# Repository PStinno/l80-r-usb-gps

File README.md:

# l80-r-usb-gps
USB GPS board using the Quectel L80-R GPS module

This board makes use of the Quectel L80-R GPS module with integratred ceramic patch antenna and the CH340 USB-to-UART IC, to allow the GPS module to be powered from a micro-USB connector and serial GPS data to be received on a connected computer. A simple python script is included in the repository for receiving the serial data and parsing it to extract speed, time, latitude/longitude etc.

[![CC BY-SA 4.0][cc-by-sa-image]][cc-by-sa]

[cc-by-sa]: http://creativecommons.org/licenses/by-sa/4.0/
[cc-by-sa-image]: https://licensebuttons.net/l/by-sa/4.0/88x31.png
[cc-by-sa-shield]: https://img.shields.io/badge/License-CC%20BY--SA%204.0-lightgrey.svg

This work is licensed under a [Creative Commons Attribution-ShareAlike 4.0 International License][cc-by-sa].

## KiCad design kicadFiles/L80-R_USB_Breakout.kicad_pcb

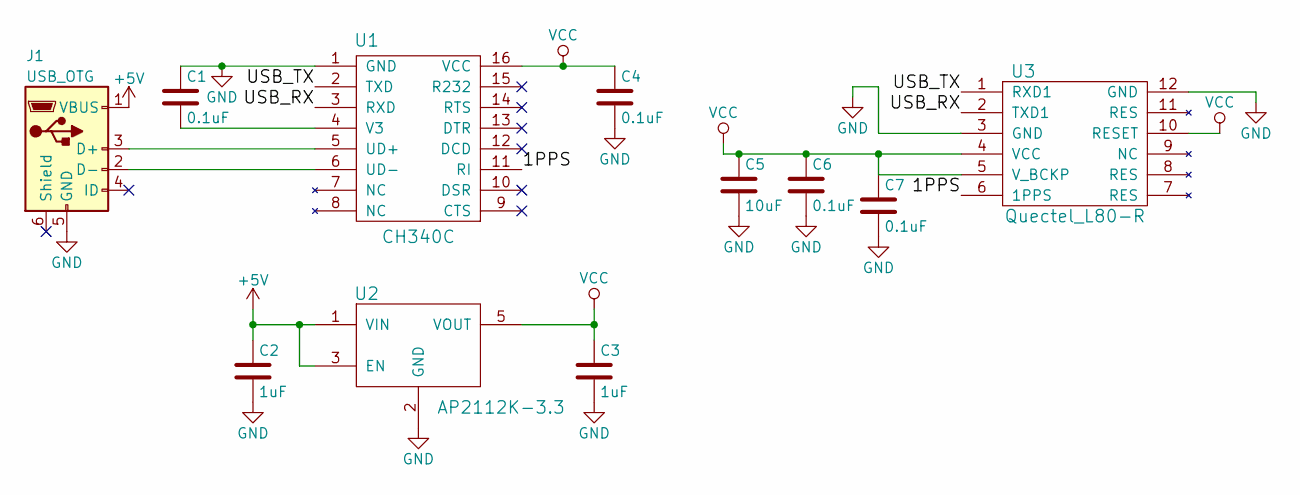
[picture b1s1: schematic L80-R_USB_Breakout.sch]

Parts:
C1, C4, C6, C7: 0.1uF; C_0603
C2, C3: 1uF; C_0603
C5: 10uF; C_0603
J1: USB_OTG; Amphenol_10118194-0001LF_Micro_USB_B
U1: CH340C; SOIC-16_3.9x9.9mm_Pitch1.27mm
U2: AP2112K-3.3; SOT-23-5
U3: Quectel_L80-R

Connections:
+5V: C2.1, J1.1 (VBUS), U2.1 (VIN), U2.3 (EN)
/1PPS: U1.11 (RI), U3.6 (1PPS)
/USB_RX: U1.3 (RXD), U3.2 (TXD1)
/USB_TX: U1.2 (TXD), U3.1 (RXD1)
GND: C1.1, C2.2, C3.2, C4.2, C5.2, C6.2, C7.2, J1.5 (GND), U1.1 (GND), U2.2 (GND), U3.3 (GND), U3.12 (GND)
unnamed: C1.2, U1.4 (V3)
unnamed: J1.2 (D-), U1.6 (UD-)
unnamed: J1.3 (D+), U1.5 (UD+)
VCC: C3.1, C4.1, C5.1, C6.1, C7.1, U1.16 (VCC), U2.5 (VOUT), U3.4 (VCC), U3.5 (V_BCKP), U3.10 (RESET)

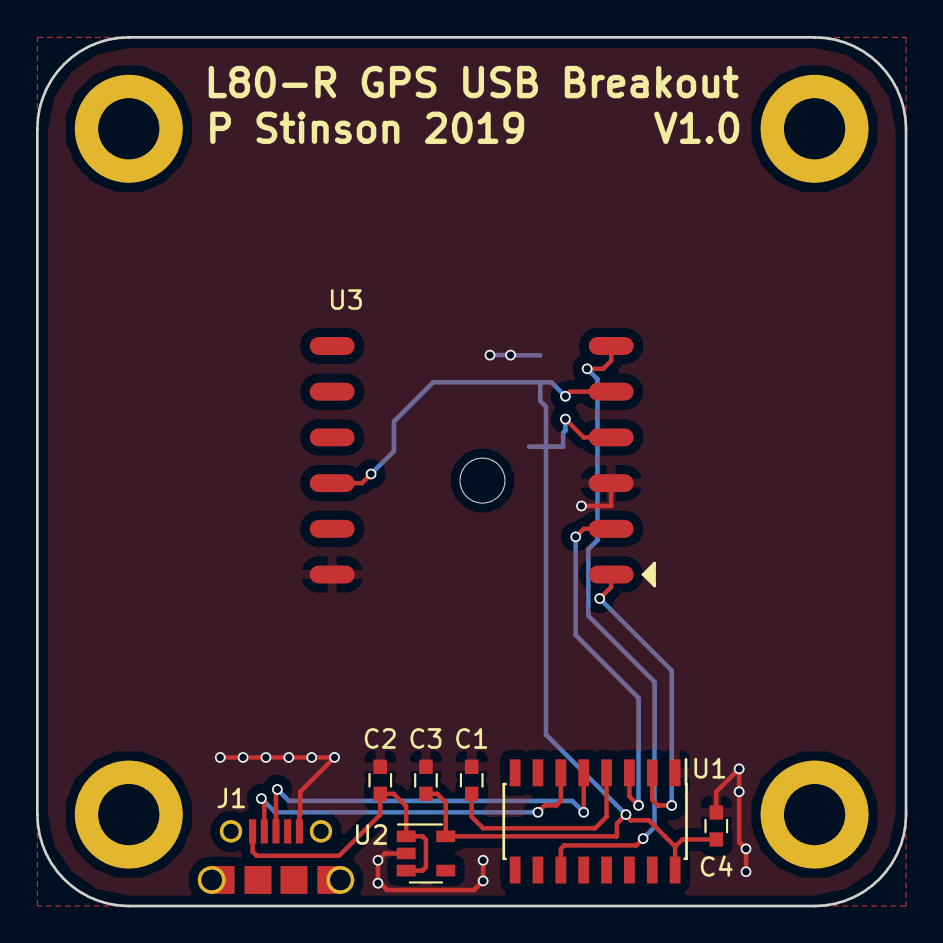
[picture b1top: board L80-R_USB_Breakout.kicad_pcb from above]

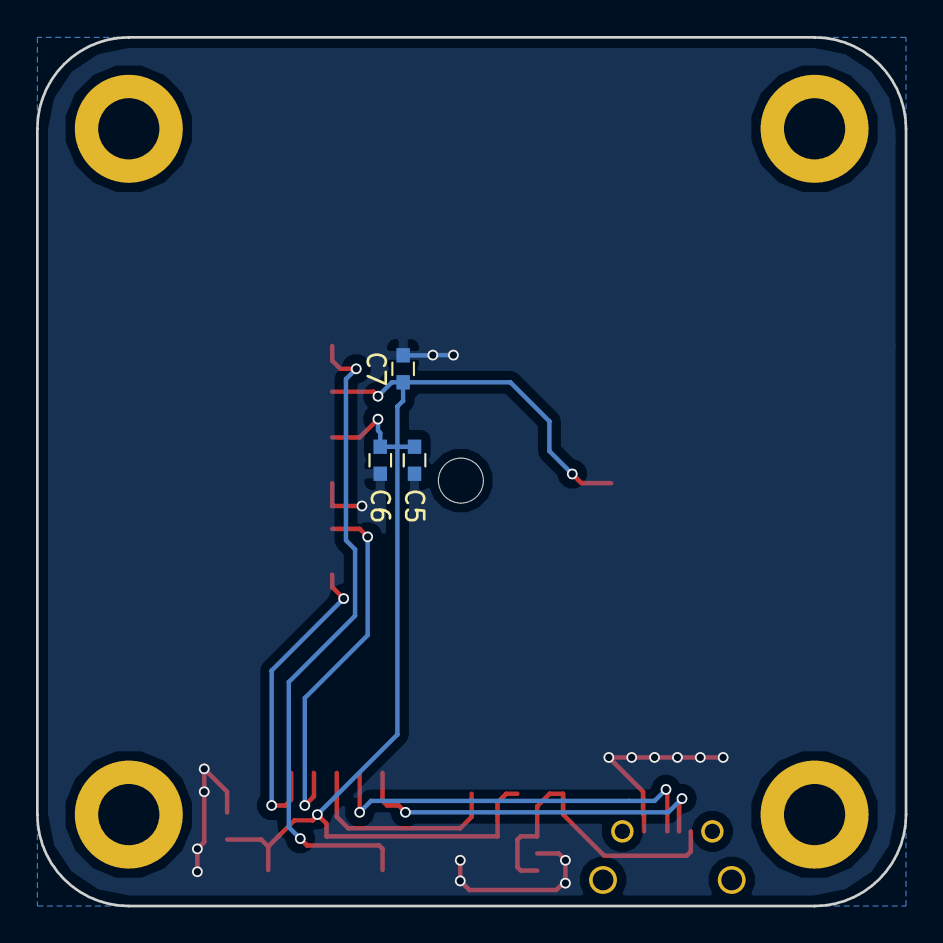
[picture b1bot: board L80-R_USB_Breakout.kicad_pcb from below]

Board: 2 copper layers, 48.3 x 48.3 mm, 11 parts (3 on the bottom side), 9 nets.

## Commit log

2022-04-19 Add PCB files, images and license
2022-04-19 Add Python Test Script
    Simple Python script to read and parse messages received from the GPS module over the serial port.
